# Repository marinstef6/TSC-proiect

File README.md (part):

**Descriere functionalitate hardware**

Proiectul are la baza microcontroller-ul ESP32-C6, care gestioneaza comunicarea cu toate componentele externe si senzorii conectati. Acest microcontroller ofera conectivitate Wifi si Bluetooth dar si suport pentru interfetele SPI, I2C si UART. Este conectat la 3.3V printr-un regulator de tensiune LDO, acesta primind energie de la o baterie Li-po de 3.7V.
Afisarea informatiile se face utilizand un display E-Paper care este conectat prin inteerfata SPI, oferind un consum redus de energie, acstea fiind mai activ doar cand se fac actualizari pentru ecran. Informatiile pe care le va afisa sunt data, ora, valori senzori etc.
Monitorizarea mediului se face cu ajutorul senzorului BME688, acesta masurand temperatura, umiditatea dar si presiunea atmosferica. Comunica cu microcontroller-ul prin magistrala I2C.
Modulul RTC DS3231 este conectat tot la I2C si mentine ora si data exacta, chiar daca sistemul va fi oprit.
Prin portul USB-C se va face alimentarea sistemuluo care este conectat la circuitul de incarcare de baterie, acesta folosind MCP73831 si astfel controland incarcarea bateriei Li-Po. Tensiunea va fi stabilita la 3.3V pentru alimentarea senzorilor si a microcontroller-ului. 
Circuitul MAX17048 este folosit pentru a monitoriza nivelul incarcarii bateriei si ofera informatii despre tensiune si starea de incarcare prin I2C.
Consumul de energie este dat de ESP32-C6 care va putea sa intre in modul de consum redus si permite functionarea pe termen lung a bateriei. Consumul in regim activ este facut in functie de sarcinile si componentele active in acel moment.
Pentru a stoca, sistemul va folosi o memorie externa de tip NOR Flash conectata cu ajutorul lui SPI dar vom avea si un slot de card SD. Acesta va fi folosit pentru a loga local datele. Butoanele sunt conectate la GPIO-uri si vor fi folosite pentru reset, boot si alte actiuni. 

**Bill Of Materials**

| Componentă            | Datasheet                                                                                                                                      | Link produs                                                                                                          |
|-----------------------|------------------------------------------------------------------------------------------------------------------------------------------------|-----------------------------------------------------------------------------------------------------------------------|
| ESP32-C6-WROOM-1-N8 | [Datasheet](https://ro.mouser.com/datasheet/2/891/Espressif_ESP32_C6_WROOM_1__Datasheet_V0_1_PRELIMI-3239987.pdf) | [Link](https://ro.mouser.com/ProductDetail/Espressif-Systems/ESP32-C6-WROOM-1-N8?qs=8Wlm6%252BaMh8ST02Gmwp74cw%3D%3D) |
| MCP73831 | [Datasheet](https://ww1.microchip.com/downloads/aemDocuments/documents/APID/ProductDocuments/DataSheets/MCP73831-Family-Data-Sheet-DS20001984H.pdf) | [Link](https://store.comet.srl.ro/Catalogue/Product/15728/) |
| MAX17048G+T10 | [Datasheet](https://ro.mouser.com/datasheet/2/609/MAX17048_MAX17049-3469099.pdf) | [Link](https://ro.mouser.com/ProductDetail/Analog-Devices-Maxim-Integrated/MAX17048G%2bT10?qs=D7PJwyCwLAoGnnn8jEPRBQ%3D%3D) |
| USBLC6-2SC6Y | [Datasheet](https://ro.mouser.com/datasheet/2/389/usblc6_2sc6y-1852505.pdf) | [Link](https://ro.mouser.com/ProductDetail/STMicroelectronics/USBLC6-2SC6Y?qs=gNDSiZmRJS%2FOgDexvXkdow%3D%3D) |
| PFMF.050.2 | [Datasheet](https://ro.mouser.com/datasheet/2/358/typ_PFMF-1275918.pdf) | [Link](https://ro.mouser.com/ProductDetail/Schurter/PFMF.050.2?qs=1auRipcfynCums5v1iucSA%3D%3D)|
| SD0805S020S1R0 | [Datasheet](https://ro.mouser.com/datasheet/2/40/schottky-3165252.pdf) | [Link](https://ro.mouser.com/ProductDetail/KYOCERA-AVX/SD0805S020S1R0?qs=jCA%252BPfw4LHbpkAoSnwrdjw%3D%3D) |
| DMG2305UX-7 | [Datasheet](https://www.diodes.com/assets/Datasheets/DMG2305UX.pdf) | [Link](https://ro.mouser.com/ProductDetail/Diodes-Incorporated/DMG2305UX-7?qs=L1DZKBg7t5F%2FNBHrjfxC%252Bg%3D%3D)|
| XC6220A331MR-G (IC4)  | [Datasheet](https://ro.mouser.com/datasheet/2/760/xc6220-3371556.pdf) | [Link](https://ro.mouser.com/ProductDetail/Torex-Semiconductor/XC6220A331MR-G?qs=AsjdqWjXhJ8ZSWznL1J0gg%3D%3D) |
| 112A-TAAR-R03 (J4) | [Datasheet](https://store.comet.bg/download-file.php?id=27596) | [Link](https://store.comet.srl.ro/Catalogue/Product/43497/)|
| MBR0530T3G | [Datasheet](https://www.onsemi.com/products/discrete-power-modules/schottky-diodes-schottky-rectifiers/mbr0530t3g) | [Link](https://ro.mouser.com/ProductDetail/onsemi/MBR0530T3G?qs=3JMERSakebpEmdUS6GetdQ%3D%3D) |  
| MCP73831-2ACI/MC (U5) | [Datasheet](https://ro.mouser.com/datasheet/2/268/MCP73831_Family_Data_Sheet_DS2001984H-3441711.pdf) | [Link](https://ro.mouser.com/ProductDetail/Microchip-Technology/MCP73831-2ACI-MC?qs=hH%252BOa0VZEiBneYTVdpuVdg%3D%3D) |
| FH34SRJ-24S-0.5SH(99) (J1) | [Datasheet](https://ro.mouser.com/datasheet/2/185/FH34SRJ_24S_0_5SH_99__CL0580_1255_6_99_2DDrawing_0-1615044.pdf) | [Link](https://ro.mouser.com/ProductDetail/Hirose-Connector/FH34SRJ-24S-0.5SH99?qs=vcbW%252B4%252BSTIpKBl5ap9J8Fw%3D%3D) |
| DMG2305UX-7 | [Datasheet](https://www.diodes.com/assets/Datasheets/DMG2305UX.pdf) | [Link](https://ro.mouser.com/ProductDetail/Diodes-Incorporated/DMG2305UX-7?qs=L1DZKBg7t5F%2FNBHrjfxC%252Bg%3D%3D) |
| BME688 | [Datasheet](https://ro.mouser.com/datasheet/2/783/bst_bme688_fl000-2307034.pdf) | [Link](https://ro.mouser.com/ProductDetail/Bosch-Sensortec/BME688?qs=IS%252B4QmGtzzqQoVDscqwx3A%3D%3D) |
| BD5229G-TR (IC1) | [Datasheet](https://fscdn.rohm.com/en/products/databook/datasheet/ic/power/voltage_detector/bd52xxg-e.pdf) | [Link](https://ro.mouser.com/ProductDetail/ROHM-Semiconductor/BD5229G-TR?qs=4kLU8WoGk0vvnhrrYwdszw%3D%3D) |
| DS3231SN# (U3) | [Datasheet](https://ro.mouser.com/datasheet/2/609/DS3231-3421123.pdf) | [Link](https://ro.mouser.com/ProductDetail/Analog-Devices-Maxim-Integrated/DS3231SN?qs=1eQvB6Dk1vhUlr8%2FOrV0Fw%3D%3D) |
| CPH3225A | [Datasheet](https://ro.mouser.com/datasheet/2/360/Seiko_Instruments_MicroBattery_E_20230330_2024Jan_-3561061.pdf) | [Link](https://ro.mouser.com/ProductDetail/Seiko-Semiconductors/CPH3225A?qs=3etwrb1wR%252BhUOph6lAO7eg%3D%3D) |
| PGB1010603MR | [Datasheet](https://www.littelfuse.com/assetdocs/pulseguard-esd-suppressors-pgb1-datasheet?assetguid=8a337998-d54d-466b-be4e-dc5bcd1f9321) | [Link](https://ro.mouser.com/ProductDetail/Littelfuse/PGB1010603MR?qs=gu7KAQ731URLg4GSnNNN7Q%3D%3D) |
| W25Q512JVEIQ (U1) | [Datasheet](https://ro.mouser.com/datasheet/2/949/Winbond_W25Q512JV_Datasheet-3240039.pdf) | [Link](https://ro.mouser.com/ProductDetail/Winbond/W25Q512JVEIQ?qs=l7cgNqFNU1jw6svr3at6tA%3D%3D) |
| Qwiic connector 4-pin Accessories (J3) | [Datasheet]() | [Link](https://ro.mouser.com/ProductDetail/Adafruit/4208?qs=sGAEpiMZZMu%252BmKbOcEVhFfAP7xIR0SjxIdzFSebeFhrPm75zJVCgyQ%3D%3D) |
| C1 | [Datasheet](https://ro.mouser.com/datasheet/2/447/UPY_GPHC_X7R_6_3V_to_250V_24-3441574.pdf) | [Link](https://ro.mouser.com/ProductDetail/YAGEO/CC0402KRX7R7BB104?qs=AgBp2OyFlx%252BSOyhfyS7hpw%3D%3D) |
| C2 | [Datasheet](https://ro.mouser.com/datasheet/2/447/UPY_GPHC_X7R_6_3V_to_250V_24-3441574.pdf) | [Link](https://ro.mouser.com/ProductDetail/YAGEO/CC0402KRX7R7BB104?qs=AgBp2OyFlx%252BSOyhfyS7hpw%3D%3D) |
| C1_BAT | [Datasheet](https://ro.mouser.com/datasheet/2/447/upy_gphc_x5r_4v_to_50v-3461255.pdf) | [Link](https://ro.mouser.com/ProductDetail/YAGEO/CC0402MPX5R5BB475?qs=mzRxyRlhVdsRoWExm6hPvg%3D%3D) |
| C1_BAT1 | [Datasheet](https://ro.mouser.com/datasheet/2/447/upy_gphc_x5r_4v_to_50v-3461255.pdf) | [Link](https://ro.mouser.com/ProductDetail/YAGEO/CC0402MPX5R5BB475?qs=mzRxyRlhVdsRoWExm6hPvg%3D%3D) |                                   
| C1_BAT2 | [Datasheet](https://ro.mouser.com/datasheet/2/447/upy_gphc_x5r_4v_to_50v-3461255.pdf) | [Link](https://ro.mouser.com/ProductDetail/YAGEO/CC0402MPX5R5BB475?qs=mzRxyRlhVdsRoWExm6hPvg%3D%3D) |  
| C2_BAT | [Datasheet](https://ro.mouser.com/datasheet/2/447/upy_gphc_x5r_4v_to_50v-3461255.pdf) | [Link](https://ro.mouser.com/ProductDetail/YAGEO/CC0402MPX5R5BB475?qs=mzRxyRlhVdsRoWExm6hPvg%3D%3D) |
| C4 | [Datasheet](https://ro.mouser.com/datasheet/2/447/upy_gphc_x5r_4v_to_50v-3461255.pdf) | [Link](https://ro.mouser.com/ProductDetail/YAGEO/CC0402KPX5R8BB105?qs=mzRxyRlhVduNCG5kLC2PGw%3D%3D) |
| C3 | [Datasheet]() | [Link]() |
| C4_USB | [Datasheet](https://ro.mouser.com/datasheet/2/447/UPY_GPHC_X7R_6_3V_to_250V_24-3441574.pdf) | [Link](https://ro.mouser.com/ProductDetail/YAGEO/CC0402KRX7R7BB104?qs=AgBp2OyFlx%252BSOyhfyS7hpw%3D%3D) |
| C5 | [Datasheet](https://ro.mouser.com/datasheet/2/447/UPY_GPHC_X6S_4V_to_50V_5-3461239.pdf) | [Link](https://ro.mouser.com/ProductDetail/YAGEO/CC0402KRX6S8BB105?qs=W0yvOO0ixfHpmgj3WKoR4Q%3D%3D) |
| C5_USB | [Datasheet](https://ro.mouser.com/datasheet/2/447/upy_gphc_x5r_4v_to_50v-3461255.pdf) | [Link](https://ro.mouser.com/ProductDetail/YAGEO/CC0402MPX5R5BB475?qs=mzRxyRlhVdsRoWExm6hPvg%3D%3D) |
| C6 | [Datasheet](https://ro.mouser.com/datasheet/2/447/UPY_GPHC_X7R_6_3V_to_250V_24-3441574.pdf) | [Link](https://ro.mouser.com/ProductDetail/YAGEO/CC0402KRX7R7BB104?qs=AgBp2OyFlx%252BSOyhfyS7hpw%3D%3D) |
| C7 | [Datasheet](https://ro.mouser.com/datasheet/2/447/upy_gphc_x5r_4v_to_50v-3461255.pdf) | [Link](https://ro.mouser.com/ProductDetail/YAGEO/CC0402MRX5R4BB106?qs=tS%2FAHvPQ%2F561gTjBOiVihQ%3D%3D) |
| C8 | [Datasheet](https://ro.mouser.com/datasheet/2/447/UPY_GPHC_X7R_6_3V_to_250V_24-3441574.pdf) | [Link](https://ro.mouser.com/ProductDetail/YAGEO/CC0402KRX7R7BB104?qs=AgBp2OyFlx%252BSOyhfyS7hpw%3D%3D) |
| C9 | [Datasheet](https://ro.mouser.com/datasheet/2/447/UPY_GPHC_X7R_6_3V_to_250V_24-3441574.pdf) | [Link](https://ro.mouser.com/ProductDetail/YAGEO/CC0402KRX7R7BB104?qs=AgBp2OyFlx%252BSOyhfyS7hpw%3D%3D) |
| C10 | [Datasheet](https://ro.mouser.com/datasheet/2/447/UPY_GPHC_X7R_6_3V_to_250V_24-3441574.pdf) | [Link](https://ro.mouser.com/ProductDetail/YAGEO/CC0402KRX7R7BB104?qs=AgBp2OyFlx%252BSOyhfyS7hpw%3D%3D) |
| C10_SUPERCAP | [Datasheet](https://ro.mouser.com/datasheet/2/360/Seiko_Instruments_MicroBattery_E_20230330_2024Jan_-3561061.pdf) | [Link](https://ro.mouser.com/ProductDetail/Seiko-Semiconductors/CPH3225A?qs=3etwrb1wR%252BhUOph6lAO7eg%3D%3D) |
| CHANGE_BUTTON | [Datasheet](https://ro.mouser.com/datasheet/2/1490/SOF_data_sheet-3304259.pdf) | [Link](https://ro.mouser.com/ProductDetail/Mitsumi/SOF-232HNT?qs=Imq1NPwxi77Mt0U54xXTVA%3D%3D) |
| RESET_BUTTON | [Datasheet](https://ro.mouser.com/datasheet/2/1490/SOF_data_sheet-3304259.pdf) | [Link](https://ro.mouser.com/ProductDetail/Mitsumi/SOF-232HNT?qs=Imq1NPwxi77Mt0U54xXTVA%3D%3D) |
| BOOT_BUTTON | [Datasheet](https://ro.mouser.com/datasheet/2/1490/SOF_data_sheet-3304259.pdf) | [Link](https://ro.mouser.com/ProductDetail/Mitsumi/SOF-232HNT?qs=Imq1NPwxi77Mt0U54xXTVA%3D%3D) |  
| CHG_LED | [Datasheet]() | [Link]() |
| C_DELAY | [Datasheet](https://ro.mouser.com/datasheet/2/447/UPY_GPHC_X7R_6_3V_to_250V_24-3441574.pdf) | [Link](https://ro.mouser.com/ProductDetail/YAGEO/CC0402KRX7R7BB104?qs=AgBp2OyFlx%252BSOyhfyS7hpw%3D%3D) |
| D2 | [Datasheet](https://ro.mouser.com/datasheet/2/40/schottky-3165252.pdf) | [Link](https://ro.mouser.com/ProductDetail/KYOCERA-AVX/SD0805S020S1R0?qs=jCA%252BPfw4LHbpkAoSnwrdjw%3D%3D) |
| D3 | [Datasheet](https://www.onsemi.com/products/discrete-power-modules/schottky-diodes-schottky-rectifiers/mbr0530t3g) | [Link](https://ro.mouser.com/ProductDetail/onsemi/MBR0530T3G?qs=3JMERSakebpEmdUS6GetdQ%3D%3D) |
| D4 | [Datasheet](https://www.onsemi.com/products/discrete-power-modules/schottky-diodes-schottky-rectifiers/mbr0530t3g) | [Link](https://ro.mouser.com/ProductDetail/onsemi/MBR0530T3G?qs=3JMERSakebpEmdUS6GetdQ%3D%3D) |
| D5 | [Datasheet](https://www.onsemi.com/products/discrete-power-modules/schottky-diodes-schottky-rectifiers/mbr0530t3g) | [Link](https://ro.mouser.com/ProductDetail/onsemi/MBR0530T3G?qs=3JMERSakebpEmdUS6GetdQ%3D%3D) |
| D6 | [Datasheet](https://www.littelfuse.com/assetdocs/pulseguard-esd-suppressors-pgb1-datasheet?assetguid=8a337998-d54d-466b-be4e-dc5bcd1f9321) | [Link](https://ro.mouser.com/ProductDetail/Littelfuse/PGB1010603MR?qs=gu7KAQ731URLg4GSnNNN7Q%3D%3D) |
| D7 | [Datasheet](https://ro.mouser.com/datasheet/2/40/schottky-3165252.pdf) | [Link](https://ro.mouser.com/ProductDetail/KYOCERA-AVX/SD0805S020S1R0?qs=jCA%252BPfw4LHbpkAoSnwrdjw%3D%3D) |
| D8 | [Datasheet](https://www.littelfuse.com/assetdocs/pulseguard-esd-suppressors-pgb1-datasheet?assetguid=8a337998-d54d-466b-be4e-dc5bcd1f9321) | [Link](https://ro.mouser.com/ProductDetail/Littelfuse/PGB1010603MR?qs=gu7KAQ731URLg4GSnNNN7Q%3D%3D) |
| D9 | [Datasheet](https://www.littelfuse.com/assetdocs/pulseguard-esd-suppressors-pgb1-datasheet?assetguid=8a337998-d54d-466b-be4e-dc5bcd1f9321) | [Link](https://ro.mouser.com/ProductDetail/Littelfuse/PGB1010603MR?qs=gu7KAQ731URLg4GSnNNN7Q%3D%3D) |
| D10 | [Datasheet](https://www.littelfuse.com/assetdocs/pulseguard-esd-suppressors-pgb1-datasheet?assetguid=8a337998-d54d-466b-be4e-dc5bcd1f9321) | [Link](https://ro.mouser.com/ProductDetail/Littelfuse/PGB1010603MR?qs=gu7KAQ731URLg4GSnNNN7Q%3D%3D) |
| D11 | [Datasheet](https://www.littelfuse.com/assetdocs/pulseguard-esd-suppressors-pgb1-datasheet?assetguid=8a337998-d54d-466b-be4e-dc5bcd1f9321) | [Link](https://ro.mouser.com/ProductDetail/Littelfuse/PGB1010603MR?qs=gu7KAQ731URLg4GSnNNN7Q%3D%3D) |
| D12 | [Datasheet](https://www.littelfuse.com/assetdocs/pulseguard-esd-suppressors-pgb1-datasheet?assetguid=8a337998-d54d-466b-be4e-dc5bcd1f9321) | [Link](https://ro.mouser.com/ProductDetail/Littelfuse/PGB1010603MR?qs=gu7KAQ731URLg4GSnNNN7Q%3D%3D) |
| EPD_C1 | [Datasheet](https://ro.mouser.com/datasheet/2/396/TAIY_S_A0012396493_1-2514439.pdf) | [Link](https://ro.mouser.com/ProductDetail/TAIYO-YUDEN/UMK105CBJ105MV-F?qs=lkMpTOwszhfe5N0wQnb5vQ%3D%3D) |
| EPD_C2 | [Datasheet](https://ro.mouser.com/datasheet/2/396/TAIY_S_A0012396493_1-2514439.pdf) | [Link](https://ro.mouser.com/ProductDetail/TAIYO-YUDEN/UMK105CBJ105MV-F?qs=lkMpTOwszhfe5N0wQnb5vQ%3D%3D) |  
| EPD_C5 | [Datasheet](https://ro.mouser.com/datasheet/2/396/TAIY_S_A0012396493_1-2514439.pdf) | [Link](https://ro.mouser.com/ProductDetail/TAIYO-YUDEN/UMK105CBJ105MV-F?qs=lkMpTOwszhfe5N0wQnb5vQ%3D%3D) |
| EPD_C6 | [Datasheet](https://ro.mouser.com/datasheet/2/396/TAIY_S_A0012396493_1-2514439.pdf) | [Link](https://ro.mouser.com/ProductDetail/TAIYO-YUDEN/UMK105CBJ105MV-F?qs=lkMpTOwszhfe5N0wQnb5vQ%3D%3D) |
| EPD_C7 | [Datasheet](https://ro.mouser.com/datasheet/2/396/TAIY_S_A0012396493_1-2514439.pdf) | [Link](https://ro.mouser.com/ProductDetail/TAIYO-YUDEN/UMK105CBJ105MV-F?qs=lkMpTOwszhfe5N0wQnb5vQ%3D%3D) |
| EPD_C8 | [Datasheet](https://ro.mouser.com/datasheet/2/396/TAIY_S_A0012396493_1-2514439.pdf) | [Link](https://ro.mouser.com/ProductDetail/TAIYO-YUDEN/UMK105CBJ105MV-F?qs=lkMpTOwszhfe5N0wQnb5vQ%3D%3D) |
| EPD_C9 | [Datasheet](https://ro.mouser.com/datasheet/2/396/TAIY_S_A0012396493_1-2514439.pdf) | [Link](https://ro.mouser.com/ProductDetail/TAIYO-YUDEN/UMK105CBJ105MV-F?qs=lkMpTOwszhfe5N0wQnb5vQ%3D%3D) |
| EPD_C10 | [Datasheet](https://ro.mouser.com/datasheet/2/396/TAIY_S_A0012396493_1-2514439.pdf) | [Link](https://ro.mouser.com/ProductDetail/TAIYO-YUDEN/UMK105CBJ105MV-F?qs=lkMpTOwszhfe5N0wQnb5vQ%3D%3D) |
| EPD_C11 | [Datasheet](https://ro.mouser.com/datasheet/2/396/TAIY_S_A0012396493_1-2514439.pdf) | [Link](https://ro.mouser.com/ProductDetail/TAIYO-YUDEN/UMK105CBJ105MV-F?qs=lkMpTOwszhfe5N0wQnb5vQ%3D%3D) |
| EPD_C12 | [Datasheet](https://ro.mouser.com/datasheet/2/396/TAIY_S_A0012396493_1-2514439.pdf) | [Link](https://ro.mouser.com/ProductDetail/TAIYO-YUDEN/UMK105CBJ105MV-F?qs=lkMpTOwszhfe5N0wQnb5vQ%3D%3D) |
| J2 | [Datasheet](https://ro.mouser.com/datasheet/2/837/GCT_USB4110_Product_Drawing___20k_cycles-3455479.pdf) | [Link](https://ro.mouser.com/ProductDetail/GCT/USB4110-GF-A?qs=KUoIvG%2F9IlYiZvIXQjyJeA%3D%3D) |
| L1 | [Datasheet](https://www.we-online.com/components/products/datasheet/744043680.pdf) | [Link](https://ro.mouser.com/ProductDetail/Wurth-Elektronik/744043680?qs=PGXP4M47uW6VkZq%252BkzjrHA%3D%3D) |
| Q1 | [Datasheet](https://www.vishay.com/docs/62424/sq2362ces.pdf) | [Link](https://ro.mouser.com/ProductDetail/Vishay-Siliconix/SQ2362CES-T1_GE3?qs=i8QVZAFTkqR3b4Fby5FULg%3D%3D) |
| Q2 | [Datasheet](https://www.vishay.com/docs/62424/sq2362ces.pdf) | [Link](https://ro.mouser.com/ProductDetail/Vishay-Siliconix/SQ2362CES-T1_GE3?qs=i8QVZAFTkqR3b4Fby5FULg%3D%3D) |
| Q3 | [Datasheet](https://www.vishay.com/docs/63399/si1308edl.pdf) | [Link](https://ro.mouser.com/ProductDetail/Vishay-Semiconductors/SI1308EDL-T1-GE3?qs=bX1%252BNvsK%2FBramh9tgpOaEw%3D%3D) |
| R1 | [Datasheet](https://www.vishay.com/docs/28726/uxa0204.pdf) | [Link](https://ro.mouser.com/ProductDetail/Vishay-Beyschlag/UXB02070G1002BCU00?qs=sGAEpiMZZMtlubZbdhIBIJxQofqEVEUOD1BSIwBO3kw%3D) |
| R1-PINH | [Datasheet](https://www.vishay.com/docs/28726/uxa0204.pdf) | [Link](https://ro.mouser.com/ProductDetail/Vishay-Beyschlag/UXB02070G1002BCU00?qs=sGAEpiMZZMtlubZbdhIBIJxQofqEVEUOD1BSIwBO3kw%3D) |  
| R1-PINH1 | [Datasheet](https://www.vishay.com/docs/28726/uxa0204.pdf) | [Link](https://ro.mouser.com/ProductDetail/Vishay-Beyschlag/UXB02070G1002BCU00?qs=sGAEpiMZZMtlubZbdhIBIJxQofqEVEUOD1BSIwBO3kw%3D) |
| R1_BAT | [Datasheet](https://www.vishay.com/docs/20024/dcrcwife3.pdf) | [Link](https://ro.mouser.com/ProductDetail/Vishay-Dale/CRCW121020R0JNEAIF?qs=sGAEpiMZZMtlubZbdhIBIAW9tqFSvq7c0jxkL%252Bmzr%2Fo%3D) |
| R1_PWRUSB | [Datasheet](https://www.vishay.com/docs/20024/dcrcwife3.pdf) | [Link](https://ro.mouser.com/ProductDetail/Vishay-Dale/CRCW1210100KJNEAIF?qs=sGAEpiMZZMtlubZbdhIBIGHLgUcK9TXfyBbx6%252B7%252BDh8%3D) |
| R2 | [Datasheet](https://ro.mouser.com/datasheet/2/210/kamaya_watc_s_a0000242430_1-1991191.pdf) | [Link](https://ro.mouser.com/ProductDetail/Walsin/WR04W2R20FTR?qs=sGAEpiMZZMtlubZbdhIBINZyO39%252BOXIf0PJ%252BLO4NFyY%3D) |
| R2-USB | [Datasheet]() | [Link]() |
| R2-USB1 | [Datasheet]() | [Link]() |
| R2_BAT | [Datasheet](https://www.vishay.com/docs/20024/dcrcwife3.pdf) | [Link](https://ro.mouser.com/ProductDetail/Vishay-Dale/CRCW20102K00JNEFIF?qs=sGAEpiMZZMtlubZbdhIBIAW9tqFSvq7cZ%252B13L5sdjvM%3D) |
| R2-PINH | [Datasheet](https://www.vishay.com/docs/28726/uxa0204.pdf) | [Link](https://ro.mouser.com/ProductDetail/Vishay-Beyschlag/UXB02070G1002BCU00?qs=sGAEpiMZZMtlubZbdhIBIJxQofqEVEUOD1BSIwBO3kw%3D) |
| R2-PINH1 | [Datasheet](https://www.vishay.com/docs/28726/uxa0204.pdf) | [Link](https://ro.mouser.com/ProductDetail/Vishay-Beyschlag/UXB02070G1002BCU00?qs=sGAEpiMZZMtlubZbdhIBIJxQofqEVEUOD1BSIwBO3kw%3D) |
| R3 | [Datasheet](https://www.vishay.com/docs/28726/uxa0204.pdf) | [Link](https://ro.mouser.com/ProductDetail/Vishay-Beyschlag/UXB02070G1002BCU00?qs=sGAEpiMZZMtlubZbdhIBIJxQofqEVEUOD1BSIwBO3kw%3D) |
| R4 | [Datasheet](https://www.vishay.com/docs/28726/uxa0204.pdf) | [Link](https://ro.mouser.com/ProductDetail/Vishay-Beyschlag/UXB02070G1002BCU00?qs=sGAEpiMZZMtlubZbdhIBIJxQofqEVEUOD1BSIwBO3kw%3D) |
| R5 | [Datasheet](https://www.vishay.com/docs/28726/uxa0204.pdf) | [Link](https://ro.mouser.com/ProductDetail/Vishay-Beyschlag/UXB02070G1002BCU00?qs=sGAEpiMZZMtlubZbdhIBIJxQofqEVEUOD1BSIwBO3kw%3D) |
| R6 | [Datasheet](https://www.vishay.com/docs/28726/uxa0204.pdf) | [Link](https://ro.mouser.com/ProductDetail/Vishay-Beyschlag/UXB02070G1002BCU00?qs=sGAEpiMZZMtlubZbdhIBIJxQofqEVEUOD1BSIwBO3kw%3D) |
| R7 | [Datasheet](https://www.vishay.com/docs/28726/uxa0204.pdf) | [Link](https://ro.mouser.com/ProductDetail/Vishay-Beyschlag/UXB02070G1002BCU00?qs=sGAEpiMZZMtlubZbdhIBIJxQofqEVEUOD1BSIwBO3kw%3D) |
| R8 | [Datasheet](https://www.vishay.com/docs/28726/uxa0204.pdf) | [Link](https://ro.mouser.com/ProductDetail/Vishay-Beyschlag/UXB02070G1002BCU00?qs=sGAEpiMZZMtlubZbdhIBIJxQofqEVEUOD1BSIwBO3kw%3D) |
| R9 | [Datasheet](https://www.vishay.com/docs/28726/uxa0204.pdf) | [Link](https://ro.mouser.com/ProductDetail/Vishay-Beyschlag/UXB02070G1002BCU00?qs=sGAEpiMZZMtlubZbdhIBIJxQofqEVEUOD1BSIwBO3kw%3D) |
| R10 | [Datasheet](https://www.vishay.com/docs/28726/uxa0204.pdf) | [Link](https://ro.mouser.com/ProductDetail/Vishay-Beyschlag/UXB02070G1002BCU00?qs=sGAEpiMZZMtlubZbdhIBIJxQofqEVEUOD1BSIwBO3kw%3D) |
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
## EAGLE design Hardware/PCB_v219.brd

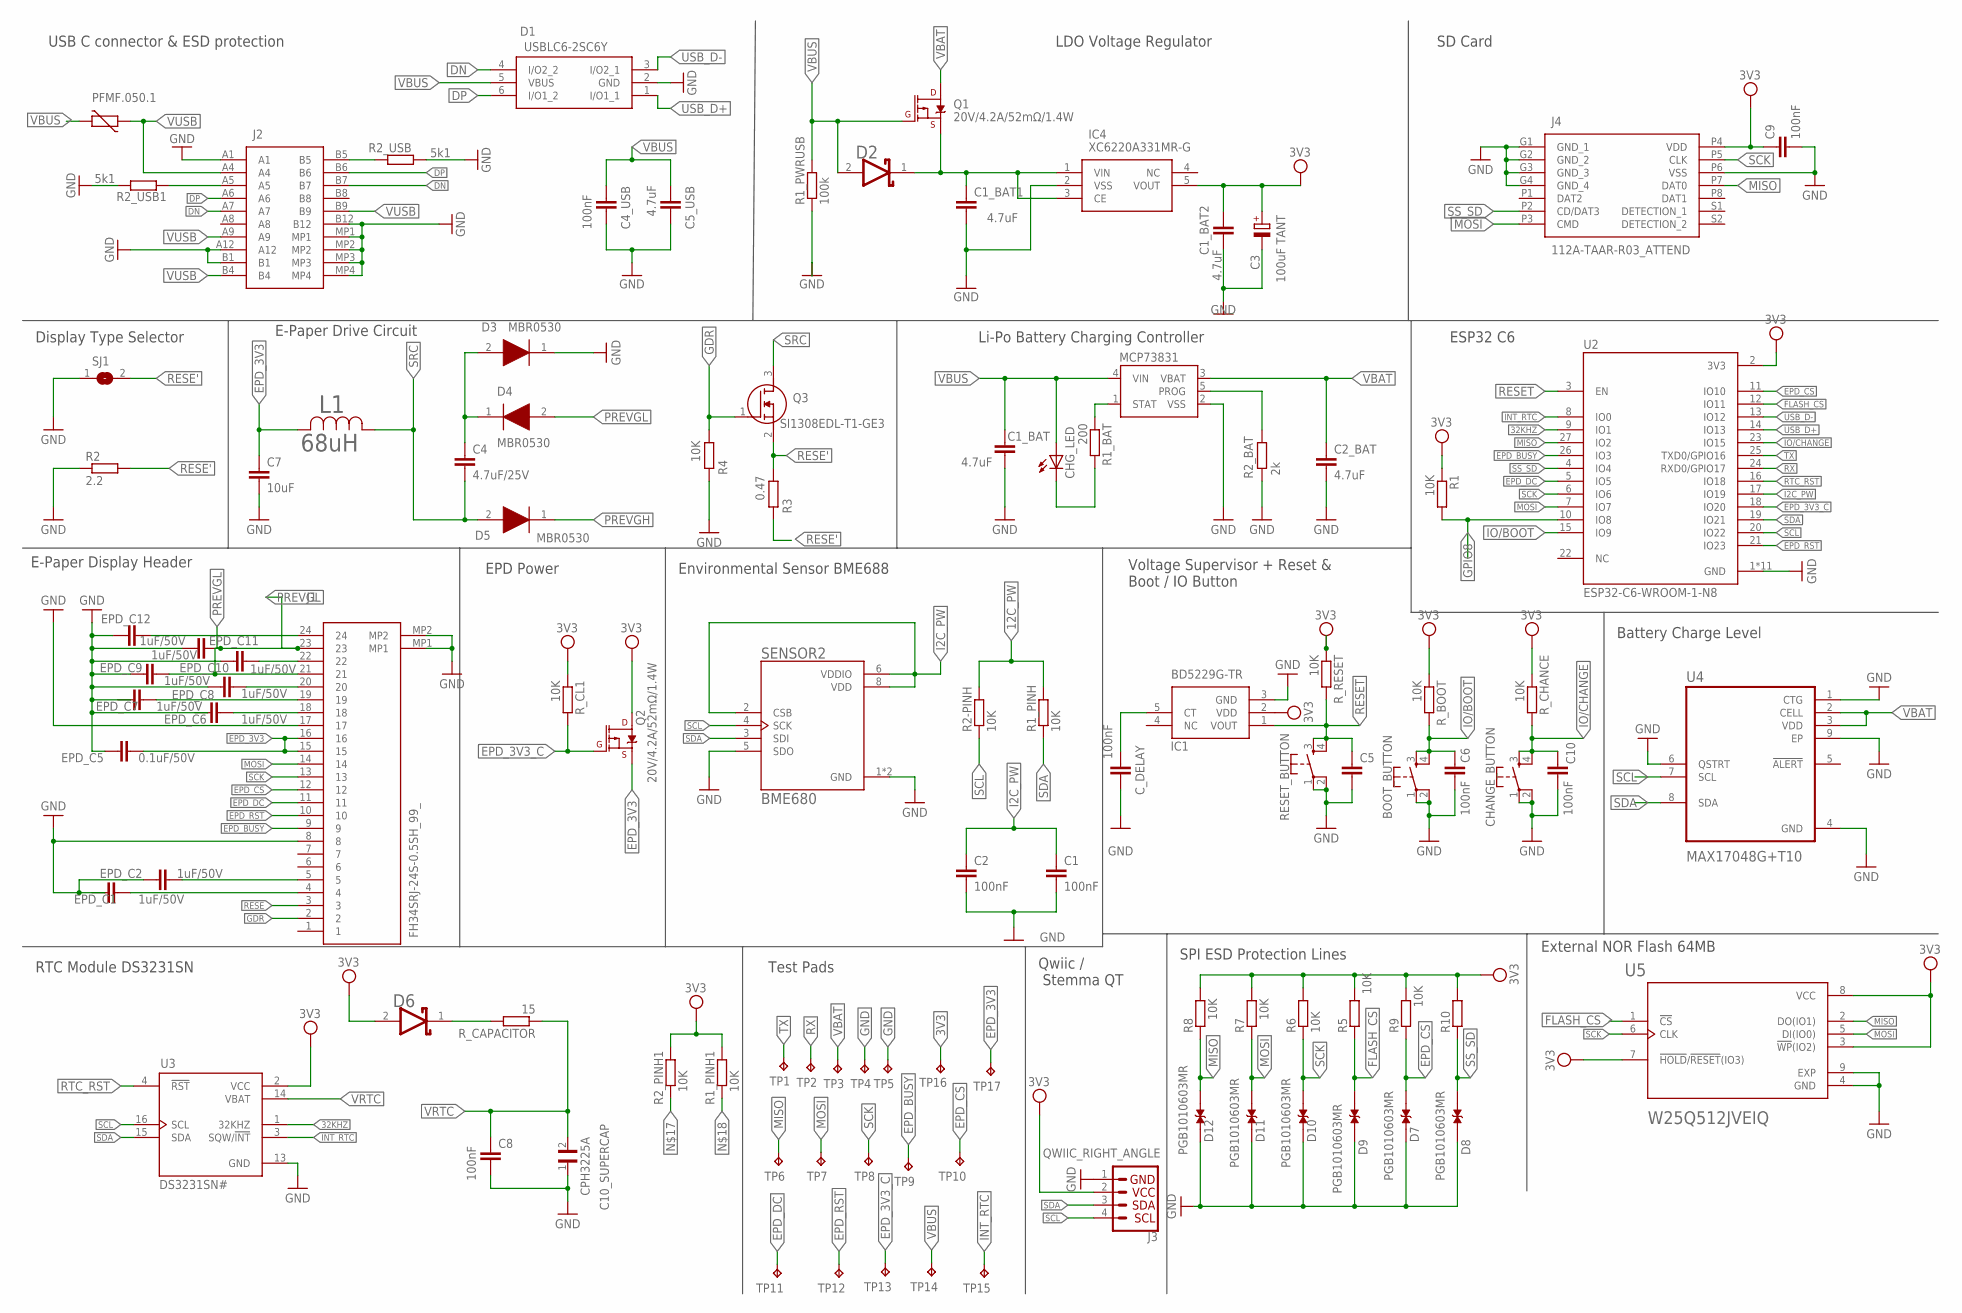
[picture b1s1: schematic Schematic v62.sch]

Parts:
BOOT_BUTTON: BUTTON_CUSYOMV1; MYBUTTON
C1, C2: 100nF; ESP32_WROVER_EAGLE-LTSPICE_C0402
C1_BAT, C1_BAT1, C1_BAT2, C5_USB: 4.7uF; EAGLE-LTSPICE_C0402
C2_BAT: 4.7uF; ESP32_WROVER_EAGLE-LTSPICE_C0402
C3: 100uF TANT; RCL_CT3528
C4: 4.7uF/25V; EAGLE-LTSPICE_C0402
C4_USB, C6, C8, C9, C10: 100nF; EAGLE-LTSPICE_C0402
C5: ESP32_WROVER_EAGLE-LTSPICE_CC0402; ESP32_WROVER_EAGLE-LTSPICE_C0402
C7: 10uF; EAGLE-LTSPICE_C0402
C10_SUPERCAP: CPH3225A; CAPCP3225X100N
CHANGE_BUTTON: BUTTON_CUSYOMV1; MYBUTTON
CHG_LED: ADAFRUIT_LEDCHIP-LED0603; ADAFRUIT_CHIP-LED0603
C_DELAY: 100nF; ESP32_WROVER_EAGLE-LTSPICE_C0402
D1: USBLC6-2SC6Y; SOT95P280X145-6N
D2: SD0805S020S1R0; ESP32_WROVER_AVX---SD0805S020S1R0_AVX_SD0805S020S1R0_0
D3, D4, D5: MBR0530; SOD3716X135N
D6: ESP32_WROVER_AVX---SD0805S020S1R0_AVX_SD0805S020S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; ESP32_WROVER_AVX---SD0805S020S1R0_AVX_SD0805S020S1R0_0
D7, D8, D9, D10, D11, D12: PGB1010603MR; DIOC1608X36N
EPD_C1, EPD_C2, EPD_C6, EPD_C7, EPD_C8, EPD_C9, EPD_C10, EPD_C11, EPD_C12: 1uF/50V; ESP32_WROVER_EAGLE-LTSPICE_C0402
EPD_C5: 0.1uF/50V; ESP32_WROVER_EAGLE-LTSPICE_C0402
IC1: BD5229G-TR; SOT95P280X125-5N
IC4: XC6220A331MR-G; SOT95P280X120-5N
J1: FH34SRJ-24S-0.5SH_99_; FH34SRJ24S05SH99
J2: SAMACSYS_PARTS_USB4110-GF-A; SAMACSYS_PARTS_USB4110GFA
J3: QWIIC_RIGHT_ANGLE; JST04_1MM_RA
J4: 112A-TAAR-R03_ATTEND; 112ATAARR03ATTEND
L1: 68uH; IND_4828-WE-TPC_WRE
PFMF.050.1: ESP32C6_VARISTORCN1812; ESP32C6_VARISTOR_CT/CN1812
Q1, Q2: 20V/4.2A/52mΩ/1.4W; ESP32_WROVER_SPARKFUN-DISCRETESEMI_SOT23-3
Q3: SI1308EDL-T1-GE3; SOT65P210X110-3N
R1, R1_PINH, R1_PINH1, R2-PINH, R2_PINH1, R4, R5, R6, R7, R8, R9, R10: 10K; ESP32_WROVER_EAGLE-LTSPICE_R0402
R1_BAT: 200; ESP32_WROVER_EAGLE-LTSPICE_R0402
R1_PWRUSB: 100k; ESP32_WROVER_EAGLE-LTSPICE_R0402
R2: 2.2; ESP32_WROVER_EAGLE-LTSPICE_R0402
R2_BAT: 2k; ESP32_WROVER_EAGLE-LTSPICE_R0402
R2_USB, R2_USB1: 5k1; ESP32_WROVER_EAGLE-LTSPICE_R0402
R3: 0.47; ESP32_WROVER_EAGLE-LTSPICE_R0402
RESET_BUTTON: BUTTON_CUSYOMV1; MYBUTTON
R_BOOT: 10K; ESP32_WROVER_EAGLE-LTSPICE_R0402
R_CAPACITOR: 15; ESP32_WROVER_EAGLE-LTSPICE_R0402
R_CHANCE: 10K; ESP32_WROVER_EAGLE-LTSPICE_R0402
R_CL1: 10K; ESP32_WROVER_EAGLE-LTSPICE_R0402
R_RESET: 10K; ESP32_WROVER_EAGLE-LTSPICE_R0402
SENSOR2: BME680; ESP32_WROVER_BME680_PSON80P300X300X100-8N
SJ1: SJ
TP1, TP2, TP3, TP4, TP5, TP6, TP7, TP8, TP9, TP10, TP11, TP12, TP13, TP14, TP15, TP16, TP17: TPTP20R; TP20R
U1: MCP73831; ESP32_WROVER_SPARKFUN-IC-POWER_SOT23-5
U2: ESP32-C6-WROOM-1-N8; XCVR_ESP32-C6-WROOM-1-N8
U3: DS3231SN#; SOIC127P1032X265-16N
U4: MAX17048G+T10; SON50P200X200X80-9N
U5: W25Q512JVEIQ; SON127P600X800X80-9N

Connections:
3V3: C1_BAT2.1, C3.+, C9.1, D6.2 (ANODE), IC1.2 (VDD), IC4.5 (VOUT), J3.2, J4.P4 (VDD), Q2.3 (D), R1.1, R1_PINH1.2, R2_PINH1.2, R5.2, R6.2, R7.2, R8.2, R9.2, R10.2, R_BOOT.1, R_CHANCE.2, R_CL1.1, R_RESET.1, TP16.TP, U2.2 (3V3), U3.2 (VCC), U5.3 (!WP!(IO2)), U5.7 (!HOLD!/!RESET!(IO3)), U5.8 (VCC)
12C_PW: R1_PINH.2, R2-PINH.2
32KHZ: U2.9 (IO1), U3.1 (32KHZ)
DN: D1.4 (I/O2_2), J2.A7, J2.B7
DP: D1.6 (I/O1_2), J2.A6, J2.B6
EPD_3V3: C7.1, EPD_C5.1, J1.15, J1.16, L1.2, Q2.2 (S), TP17.TP
EPD_3V3_C: Q2.1 (G), R_CL1.2, TP13.TP, U2.18 (IO20)
EPD_BUSY: J1.9, TP9.TP, U2.26 (IO3)
EPD_CS: D7.2, J1.12, R9.1, TP10.TP, U2.11 (IO10)
EPD_DC: J1.11, TP11.TP, U2.5 (IO5)
EPD_RST: J1.10, TP12.TP, U2.21 (IO23)
FLASH_CS: D9.2, R5.1, U2.12 (IO11), U5.1 (!CS)
GDR: J1.2, Q3.1 (G), R4.2
GND: BOOT_BUTTON.1, BOOT_BUTTON.2, C1.2, C1_BAT.2, C1_BAT1.2, C1_BAT2.2, C2.2, C2_BAT.2, C3.-, C4_USB.2, C5.2, C5_USB.2, C6.2, C7.2, C8.2, C9.2, C10.2, C10_SUPERCAP.1, CHANGE_BUTTON.1, CHANGE_BUTTON.2, C_DELAY.2, D1.2 (GND), D3.1 (K), D7.1, D8.1, D9.1, D10.1, D11.1, D12.1, EPD_C1.2, EPD_C2.2, EPD_C5.2, EPD_C6.2, EPD_C7.2, EPD_C8.2, EPD_C9.2, EPD_C10.2, EPD_C11.2, EPD_C12.2, IC1.3 (GND), IC4.2 (VSS), J1.8, J1.17, J1.MP1, J1.MP2, J2.A1, J2.A12, J2.B1, J2.B12, J2.MP1, J2.MP2, J2.MP3, J2.MP4, J3.1, J4.G1 (GND_1), J4.G2 (GND_2), J4.G3 (GND_3), J4.G4 (GND_4), J4.P6 (VSS), R1_PWRUSB.1, R2.1, R2_BAT.2, R2_USB.2, R2_USB1.1, R4.1, RESET_BUTTON.1, RESET_BUTTON.2, SENSOR2.1 (GND), SENSOR2.5 (SDO), SENSOR2.7 (GND), SJ1.1, TP4.TP, TP5.TP, U1.2 (VSS), U2.1 (GND), U2.28 (GND), U2.29_1 (GND), U2.29_2 (GND), U2.29_3 (GND), U2.29_4 (GND), U2.29_5 (GND), U2.29_6 (GND), U2.29_7 (GND), U2.29_8 (GND), U2.29_9 (GND), U3.13 (GND), U4.1 (CTG), U4.4 (GND), U4.6 (QSTRT), U4.9 (EP), U5.4 (GND), U5.9 (EXP)
GPIO8: R1.2, U2.10 (IO8)
I2C_PW: C1.1, C2.1, SENSOR2.2 (CSB), SENSOR2.6 (VDDIO), SENSOR2.8 (VDD), U2.17 (IO19)
INT_RTC: TP15.TP, U2.8 (IO0), U3.3 (SQW/!INT)
IO/BOOT: BOOT_BUTTON.3, BOOT_BUTTON.4, C6.1, R_BOOT.2, U2.15 (IO9)
IO/CHANGE: C10.1, CHANGE_BUTTON.3, CHANGE_BUTTON.4, R_CHANCE.1, U2.23 (IO15)
MISO: D12.2, J4.P7 (DAT0), R8.1, TP6.TP, U2.27 (IO2), U5.2 (DO(IO1))
MOSI: D11.2, J1.14, J4.P3 (CMD), R7.1, TP7.TP, U2.7 (IO7), U5.5 (DI(IO0))
unnamed: J2.B5, R2_USB.1
unnamed: J2.A5, R2_USB1.2
unnamed: C1_BAT1.1, D2.1 (CATHODE), IC4.1 (VIN), IC4.3 (CE), Q1.2 (S)
unnamed: C4.1, D3.2 (A), D4.1 (K)
unnamed: R1_BAT.1, U1.1 (STAT)
unnamed: CHG_LED.C, R1_BAT.2
unnamed: EPD_C12.1, J1.24
unnamed: R2_BAT.1, U1.5 (PROG)
unnamed: D6.1 (CATHODE), R_CAPACITOR.2
unnamed: EPD_C10.1, J1.22
unnamed: C_DELAY.1, IC1.5 (CT)
unnamed: EPD_C8.1, J1.20
unnamed: EPD_C7.1, J1.19
unnamed: EPD_C6.1, J1.18
unnamed: EPD_C2.1, J1.5
RESE: J1.3
RESE': Q3.2 (S), R2.2, R3.1, R3.2, SJ1.2
RESET: C5.1, IC1.1 (VOUT), RESET_BUTTON.3, RESET_BUTTON.4, R_RESET.2, U2.3 (EN)
RTC_RST: U2.16 (IO18), U3.4 (!RST)
RX: TP2.TP, U2.24 (RXD0/GPIO17)
SCK: D10.2, J1.13, J4.P5 (CLK), R6.1, TP8.TP, U2.6 (IO6), U5.6 (CLK)
SCL: J3.4, R2-PINH.1, SENSOR2.4 (SCK), U2.20 (IO22), U3.16 (SCL), U4.7 (SCL)
SDA: J3.3, R1_PINH.1, SENSOR2.3 (SDI), U2.19 (IO21), U3.15 (SDA), U4.8 (SDA)
SRC: C4.2, D5.2 (A), L1.1, Q3.3 (D)
SS_SD: D8.2, J4.P2 (CD/DAT3), R10.1, U2.4 (IO4)
TX: TP1.TP, U2.25 (TXD0/GPIO16)
USB_D+: D1.1 (I/O1_1), U2.14 (IO13)
USB_D-: D1.3 (I/O2_1), U2.13 (IO12)
VBAT: C2_BAT.1, Q1.3 (D), TP3.TP, U1.3 (VBAT), U4.2 (CELL), U4.3 (VDD)
VBUS: C1_BAT.1, C4_USB.1, C5_USB.1, CHG_LED.A, D1.5 (VBUS), D2.2 (ANODE), PFMF.050.1.2, Q1.1 (G), R1_PWRUSB.2, TP14.TP, U1.4 (VIN)
VRTC: C8.1, C10_SUPERCAP.2, R_CAPACITOR.1, U3.14 (VBAT)
VUSB: J2.A4, J2.A9, J2.B4, J2.B9, PFMF.050.1.1

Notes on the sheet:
USB C connector & ESD protection
LDO Voltage Regulator
SD Card
Display Type Selector
E-Paper Drive Circuit
Li-Po Battery Charging Controller
ESP32 C6
E-Paper Display Header
EPD Power
Environmental Sensor BME688
Voltage Supervisor + Reset & Boot / IO Button
Battery Charge Level
RTC Module DS3231SN
Test Pads
Qwiic / Stemma QT
SPI ESD Protection Lines
External NOR Flash 64MB

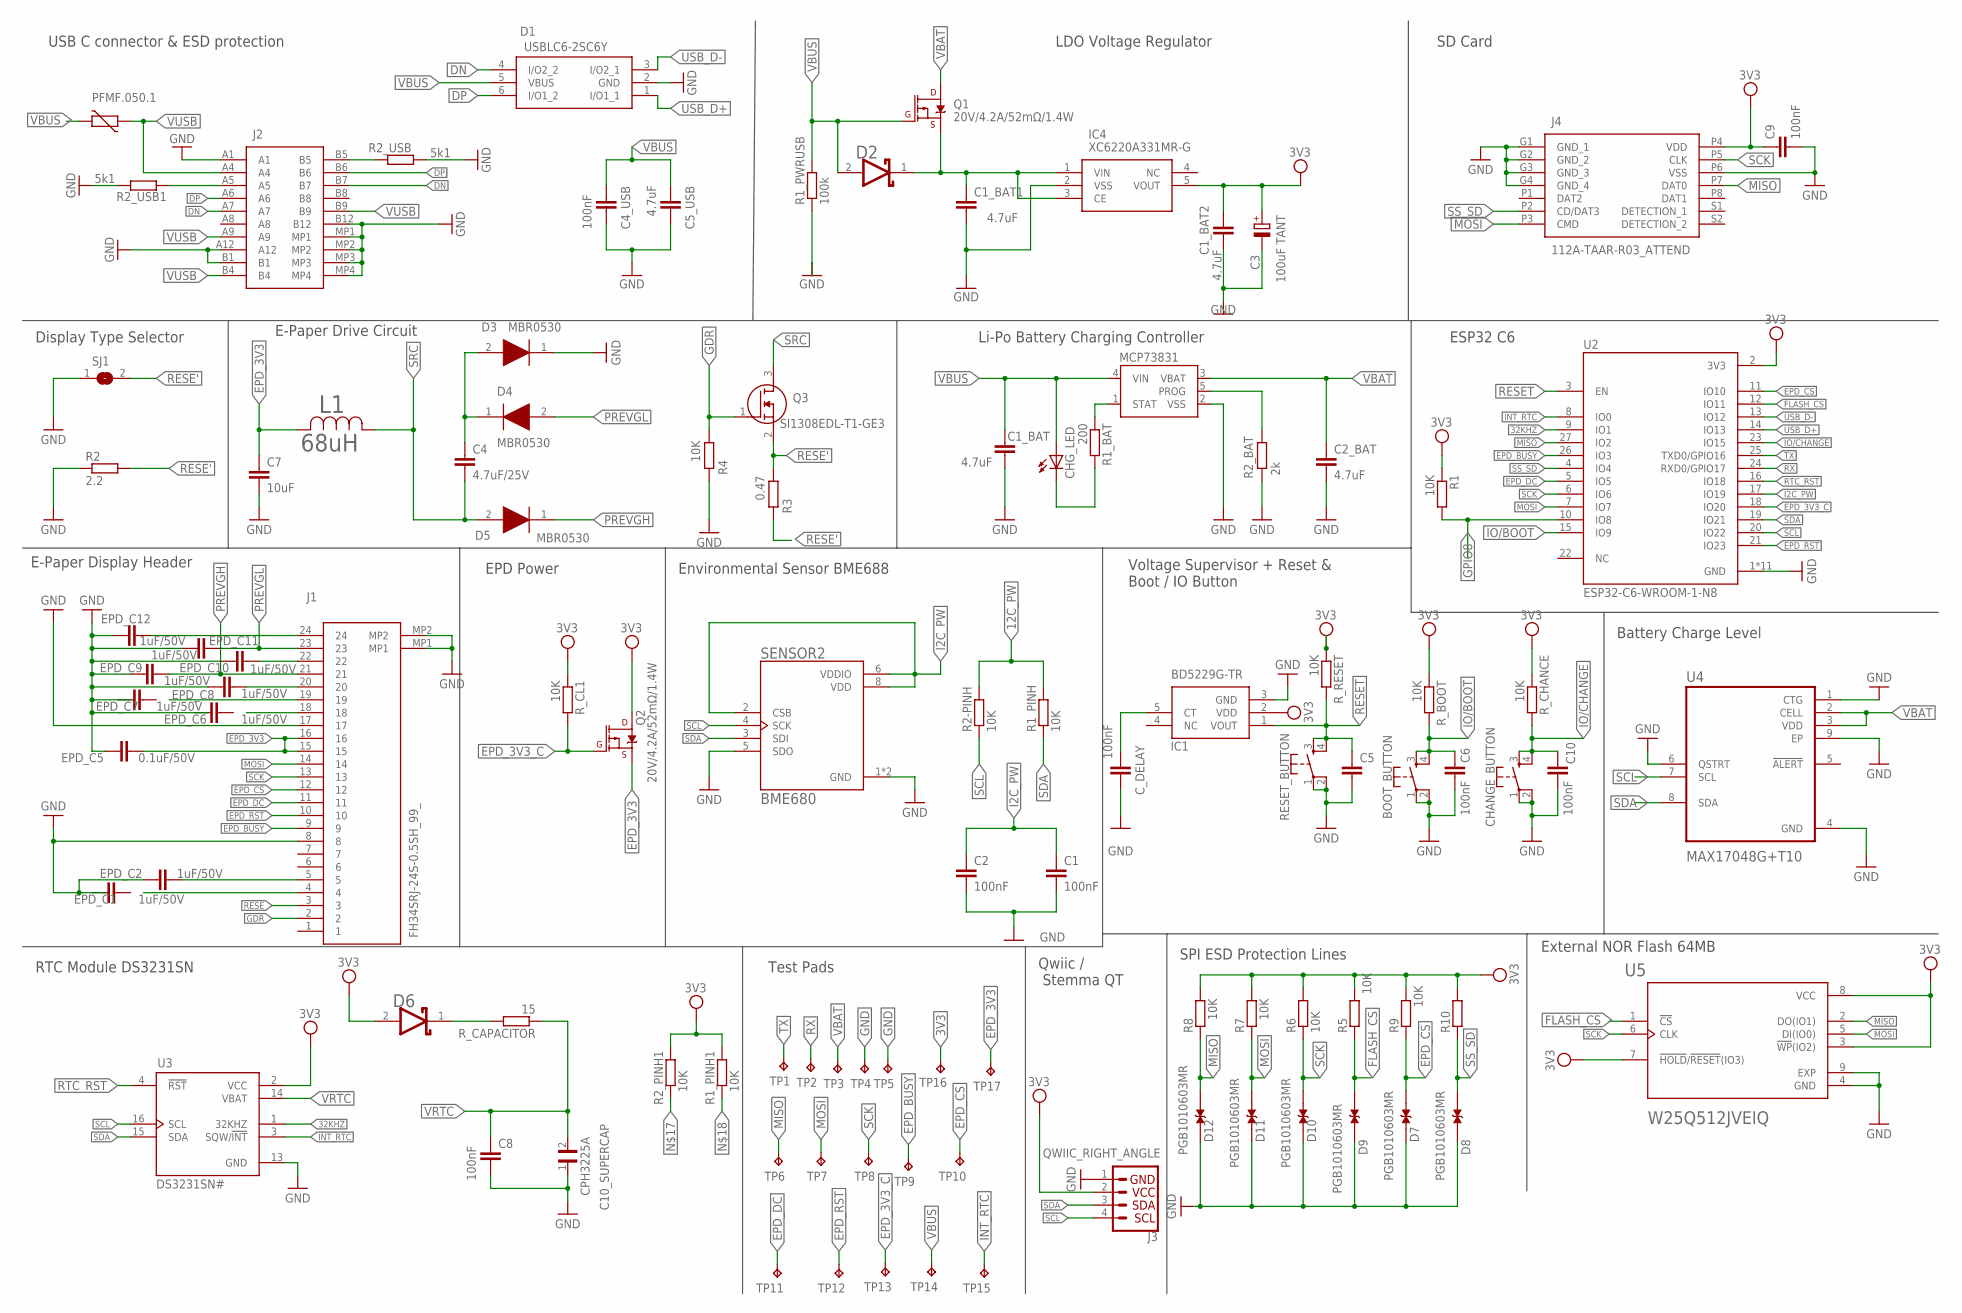
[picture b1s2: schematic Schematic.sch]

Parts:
BOOT_BUTTON: BUTTON_CUSYOMV1; MYBUTTON
C1, C2: 100nF; ESP32_WROVER_EAGLE-LTSPICE_C0402
C1_BAT, C1_BAT1, C1_BAT2, C5_USB: 4.7uF; EAGLE-LTSPICE_C0402
C2_BAT: 4.7uF; ESP32_WROVER_EAGLE-LTSPICE_C0402
C3: 100uF TANT; RCL_CT3528
C4: 4.7uF/25V; EAGLE-LTSPICE_C0402
C4_USB, C6, C8, C9, C10: 100nF; EAGLE-LTSPICE_C0402
C5: ESP32_WROVER_EAGLE-LTSPICE_CC0402; ESP32_WROVER_EAGLE-LTSPICE_C0402
C7: 10uF; EAGLE-LTSPICE_C0402
C10_SUPERCAP: CPH3225A; CAPCP3225X100N
CHANGE_BUTTON: BUTTON_CUSYOMV1; MYBUTTON
CHG_LED: ADAFRUIT_LEDCHIP-LED0603; ADAFRUIT_CHIP-LED0603
C_DELAY: 100nF; ESP32_WROVER_EAGLE-LTSPICE_C0402
D1: USBLC6-2SC6Y; SOT95P280X145-6N
D2: SD0805S020S1R0; ESP32_WROVER_AVX---SD0805S020S1R0_AVX_SD0805S020S1R0_0
D3, D4, D5: MBR0530; SOD3716X135N
D6: ESP32_WROVER_AVX---SD0805S020S1R0_AVX_SD0805S020S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; ESP32_WROVER_AVX---SD0805S020S1R0_AVX_SD0805S020S1R0_0
D7, D8, D9, D10, D11, D12: PGB1010603MR; DIOC1608X36N
EPD_C1, EPD_C2, EPD_C6, EPD_C7, EPD_C8, EPD_C9, EPD_C10, EPD_C11, EPD_C12: 1uF/50V; ESP32_WROVER_EAGLE-LTSPICE_C0402
EPD_C5: 0.1uF/50V; ESP32_WROVER_EAGLE-LTSPICE_C0402
IC1: BD5229G-TR; SOT95P280X125-5N
IC4: XC6220A331MR-G; SOT95P280X120-5N
J1: FH34SRJ-24S-0.5SH_99_; FH34SRJ24S05SH99
J2: SAMACSYS_PARTS_USB4110-GF-A; SAMACSYS_PARTS_USB4110GFA
J3: QWIIC_RIGHT_ANGLE; JST04_1MM_RA
J4: 112A-TAAR-R03_ATTEND; 112ATAARR03ATTEND
L1: 68uH; IND_4828-WE-TPC_WRE
PFMF.050.1: ESP32C6_VARISTORCN1812; ESP32C6_VARISTOR_CT/CN1812
Q1, Q2: 20V/4.2A/52mΩ/1.4W; ESP32_WROVER_SPARKFUN-DISCRETESEMI_SOT23-3
Q3: SI1308EDL-T1-GE3; SOT65P210X110-3N
R1, R1_PINH, R1_PINH1, R2-PINH, R2_PINH1, R4, R5, R6, R7, R8, R9, R10: 10K; ESP32_WROVER_EAGLE-LTSPICE_R0402
R1_BAT: 200; ESP32_WROVER_EAGLE-LTSPICE_R0402
R1_PWRUSB: 100k; ESP32_WROVER_EAGLE-LTSPICE_R0402
R2: 2.2; ESP32_WROVER_EAGLE-LTSPICE_R0402
R2_BAT: 2k; ESP32_WROVER_EAGLE-LTSPICE_R0402
R2_USB, R2_USB1: 5k1; ESP32_WROVER_EAGLE-LTSPICE_R0402
R3: 0.47; ESP32_WROVER_EAGLE-LTSPICE_R0402
RESET_BUTTON: BUTTON_CUSYOMV1; MYBUTTON
R_BOOT: 10K; ESP32_WROVER_EAGLE-LTSPICE_R0402
R_CAPACITOR: 15; ESP32_WROVER_EAGLE-LTSPICE_R0402
R_CHANCE: 10K; ESP32_WROVER_EAGLE-LTSPICE_R0402
R_CL1: 10K; ESP32_WROVER_EAGLE-LTSPICE_R0402
R_RESET: 10K; ESP32_WROVER_EAGLE-LTSPICE_R0402
SENSOR2: BME680; ESP32_WROVER_BME680_PSON80P300X300X100-8N
SJ1: SJ
TP1, TP2, TP3, TP4, TP5, TP6, TP7, TP8, TP9, TP10, TP11, TP12, TP13, TP14, TP15, TP16, TP17: TPTP20R; TP20R
U1: MCP73831; ESP32_WROVER_SPARKFUN-IC-POWER_SOT23-5
U2: ESP32-C6-WROOM-1-N8; XCVR_ESP32-C6-WROOM-1-N8
U3: DS3231SN#; SOIC127P1032X265-16N
U4: MAX17048G+T10; SON50P200X200X80-9N
U5: W25Q512JVEIQ; SON127P600X800X80-9N

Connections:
3V3: C1_BAT2.1, C3.+, C9.1, D6.2 (ANODE), IC1.2 (VDD), IC4.5 (VOUT), J3.2, J4.P4 (VDD), Q2.3 (D), R1.1, R1_PINH1.2, R2_PINH1.2, R5.2, R6.2, R7.2, R8.2, R9.2, R10.2, R_BOOT.1, R_CHANCE.2, R_CL1.1, R_RESET.1, TP16.TP, U2.2 (3V3), U3.2 (VCC), U5.3 (!WP!(IO2)), U5.7 (!HOLD!/!RESET!(IO3)), U5.8 (VCC)
12C_PW: R1_PINH.2, R2-PINH.2
32KHZ: U2.9 (IO1), U3.1 (32KHZ)
DN: D1.4 (I/O2_2), J2.A7, J2.B7
DP: D1.6 (I/O1_2), J2.A6, J2.B6
EPD_3V3: C7.1, EPD_C5.1, J1.15, J1.16, L1.2, Q2.2 (S), TP17.TP
EPD_3V3_C: Q2.1 (G), R_CL1.2, TP13.TP, U2.18 (IO20)
EPD_BUSY: J1.9, TP9.TP, U2.26 (IO3)
EPD_CS: D7.2, J1.12, R9.1, TP10.TP, U2.11 (IO10)
EPD_DC: J1.11, TP11.TP, U2.5 (IO5)
EPD_RST: J1.10, TP12.TP, U2.21 (IO23)
FLASH_CS: D9.2, R5.1, U2.12 (IO11), U5.1 (!CS)
GDR: J1.2, Q3.1 (G), R4.2
GND: BOOT_BUTTON.1, BOOT_BUTTON.2, C1.2, C1_BAT.2, C1_BAT1.2, C1_BAT2.2, C2.2, C2_BAT.2, C3.-, C4_USB.2, C5.2, C5_USB.2, C6.2, C7.2, C8.2, C9.2, C10.2, C10_SUPERCAP.1, CHANGE_BUTTON.1, CHANGE_BUTTON.2, C_DELAY.2, D1.2 (GND), D3.1 (K), D7.1, D8.1, D9.1, D10.1, D11.1, D12.1, EPD_C1.2, EPD_C2.2, EPD_C5.2, EPD_C6.2, EPD_C7.2, EPD_C8.2, EPD_C9.2, EPD_C10.2, EPD_C11.2, EPD_C12.2, IC1.3 (GND), IC4.2 (VSS), J1.8, J1.17, J1.MP1, J1.MP2, J2.A1, J2.A12, J2.B1, J2.B12, J2.MP1, J2.MP2, J2.MP3, J2.MP4, J3.1, J4.G1 (GND_1), J4.G2 (GND_2), J4.G3 (GND_3), J4.G4 (GND_4), J4.P6 (VSS), R1_PWRUSB.1, R2.1, R2_BAT.2, R2_USB.2, R2_USB1.1, R4.1, RESET_BUTTON.1, RESET_BUTTON.2, SENSOR2.1 (GND), SENSOR2.5 (SDO), SENSOR2.7 (GND), SJ1.1, TP4.TP, TP5.TP, U1.2 (VSS), U2.1 (GND), U2.28 (GND), U2.29_1 (GND), U2.29_2 (GND), U2.29_3 (GND), U2.29_4 (GND), U2.29_5 (GND), U2.29_6 (GND), U2.29_7 (GND), U2.29_8 (GND), U2.29_9 (GND), U3.13 (GND), U4.1 (CTG), U4.4 (GND), U4.6 (QSTRT), U4.9 (EP), U5.4 (GND), U5.9 (EXP)
GPIO8: R1.2, U2.10 (IO8)
I2C_PW: C1.1, C2.1, SENSOR2.2 (CSB), SENSOR2.6 (VDDIO), SENSOR2.8 (VDD), U2.17 (IO19)
INT_RTC: TP15.TP, U2.8 (IO0), U3.3 (SQW/!INT)
IO/BOOT: BOOT_BUTTON.3, BOOT_BUTTON.4, C6.1, R_BOOT.2, U2.15 (IO9)
IO/CHANGE: C10.1, CHANGE_BUTTON.3, CHANGE_BUTTON.4, R_CHANCE.1, U2.23 (IO15)
MISO: D12.2, J4.P7 (DAT0), R8.1, TP6.TP, U2.27 (IO2), U5.2 (DO(IO1))
MOSI: D11.2, J1.14, J4.P3 (CMD), R7.1, TP7.TP, U2.7 (IO7), U5.5 (DI(IO0))
unnamed: J2.B5, R2_USB.1
unnamed: J2.A5, R2_USB1.2
unnamed: C1_BAT1.1, D2.1 (CATHODE), IC4.1 (VIN), IC4.3 (CE), Q1.2 (S)
unnamed: C4.1, D3.2 (A), D4.1 (K)
unnamed: R1_BAT.1, U1.1 (STAT)
unnamed: CHG_LED.C, R1_BAT.2
unnamed: EPD_C12.1, J1.24
unnamed: R2_BAT.1, U1.5 (PROG)
unnamed: D6.1 (CATHODE), R_CAPACITOR.2
unnamed: EPD_C10.1, J1.22
unnamed: C_DELAY.1, IC1.5 (CT)
unnamed: EPD_C8.1, J1.20
unnamed: EPD_C7.1, J1.19
unnamed: EPD_C6.1, J1.18
unnamed: EPD_C2.1, J1.5
RESE: J1.3
RESE': Q3.2 (S), R2.2, R3.1, R3.2, SJ1.2
RESET: C5.1, IC1.1 (VOUT), RESET_BUTTON.3, RESET_BUTTON.4, R_RESET.2, U2.3 (EN)
RTC_RST: U2.16 (IO18), U3.4 (!RST)
RX: TP2.TP, U2.24 (RXD0/GPIO17)
SCK: D10.2, J1.13, J4.P5 (CLK), R6.1, TP8.TP, U2.6 (IO6), U5.6 (CLK)
SCL: J3.4, R2-PINH.1, SENSOR2.4 (SCK), U2.20 (IO22), U3.16 (SCL), U4.7 (SCL)
SDA: J3.3, R1_PINH.1, SENSOR2.3 (SDI), U2.19 (IO21), U3.15 (SDA), U4.8 (SDA)
SRC: C4.2, D5.2 (A), L1.1, Q3.3 (D)
SS_SD: D8.2, J4.P2 (CD/DAT3), R10.1, U2.4 (IO4)
TX: TP1.TP, U2.25 (TXD0/GPIO16)
USB_D+: D1.1 (I/O1_1), U2.14 (IO13)
USB_D-: D1.3 (I/O2_1), U2.13 (IO12)
VBAT: C2_BAT.1, Q1.3 (D), TP3.TP, U1.3 (VBAT), U4.2 (CELL), U4.3 (VDD)
VBUS: C1_BAT.1, C4_USB.1, C5_USB.1, CHG_LED.A, D1.5 (VBUS), D2.2 (ANODE), PFMF.050.1.2, Q1.1 (G), R1_PWRUSB.2, TP14.TP, U1.4 (VIN)
VRTC: C8.1, C10_SUPERCAP.2, R_CAPACITOR.1, U3.14 (VBAT)
VUSB: J2.A4, J2.A9, J2.B4, J2.B9, PFMF.050.1.1

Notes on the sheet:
USB C connector & ESD protection
LDO Voltage Regulator
SD Card
Display Type Selector
E-Paper Drive Circuit
Li-Po Battery Charging Controller
ESP32 C6
E-Paper Display Header
EPD Power
Environmental Sensor BME688
Voltage Supervisor + Reset & Boot / IO Button
Battery Charge Level
RTC Module DS3231SN
Test Pads
Qwiic / Stemma QT
SPI ESD Protection Lines
External NOR Flash 64MB

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
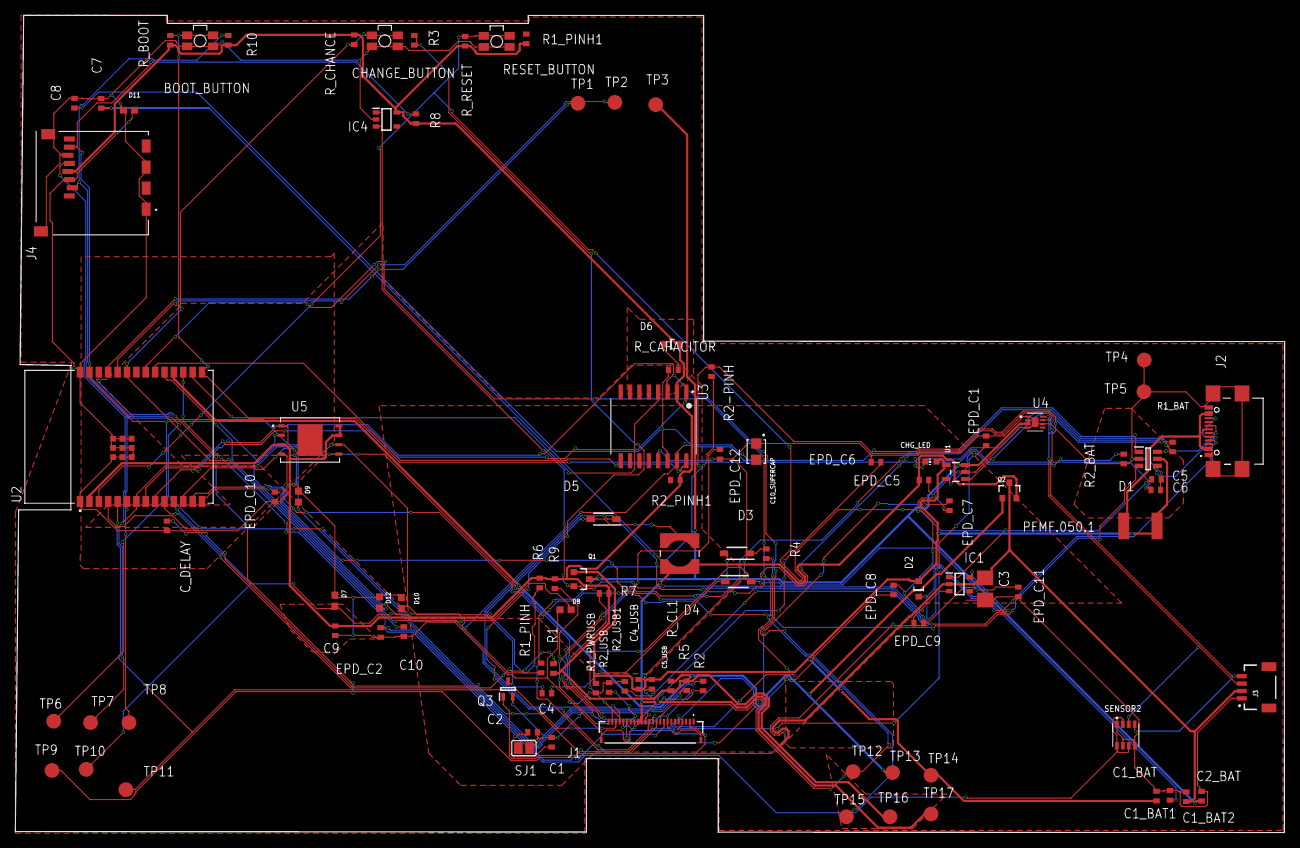
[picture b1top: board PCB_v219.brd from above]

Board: 2 copper layers, 171.8 x 110.6 mm, 103 parts (0 on the bottom side), 54 nets.

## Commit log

2025-04-01 Add files via upload
    pcb(cu plan de masa) + schematic
2025-04-01 Add files via upload
    baterie+ecran
2025-04-01 Add files via upload
    cateva imagini
2025-04-01 Add files via upload
    Am scapat de niste erori
2025-04-01 Add files via upload
    Am adaugat elementele 3d pe placa
2025-04-01 Add files via upload
    Finalul aici
2025-04-02 Add files via upload
    Acum este finalul cu componente 3d incarcate
2025-04-02 Add files via upload
    placa 3d completa
2025-04-02 Add files via upload
    componentele 3d pentru placa
2025-04-05 Proiect final .step si f3z
2025-04-05 Proiect FINAAAAL
2025-04-05 Proiect FINAL!
2025-04-05 Proiect FINALgit add .
2025-04-12 Proiect FINAL
2025-04-12 Add files via upload
    schematic final

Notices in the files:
parts and their libraries:
COPYRIGHT: Copyright (C) 2024 Ultra Librarian. All rights reserved.
